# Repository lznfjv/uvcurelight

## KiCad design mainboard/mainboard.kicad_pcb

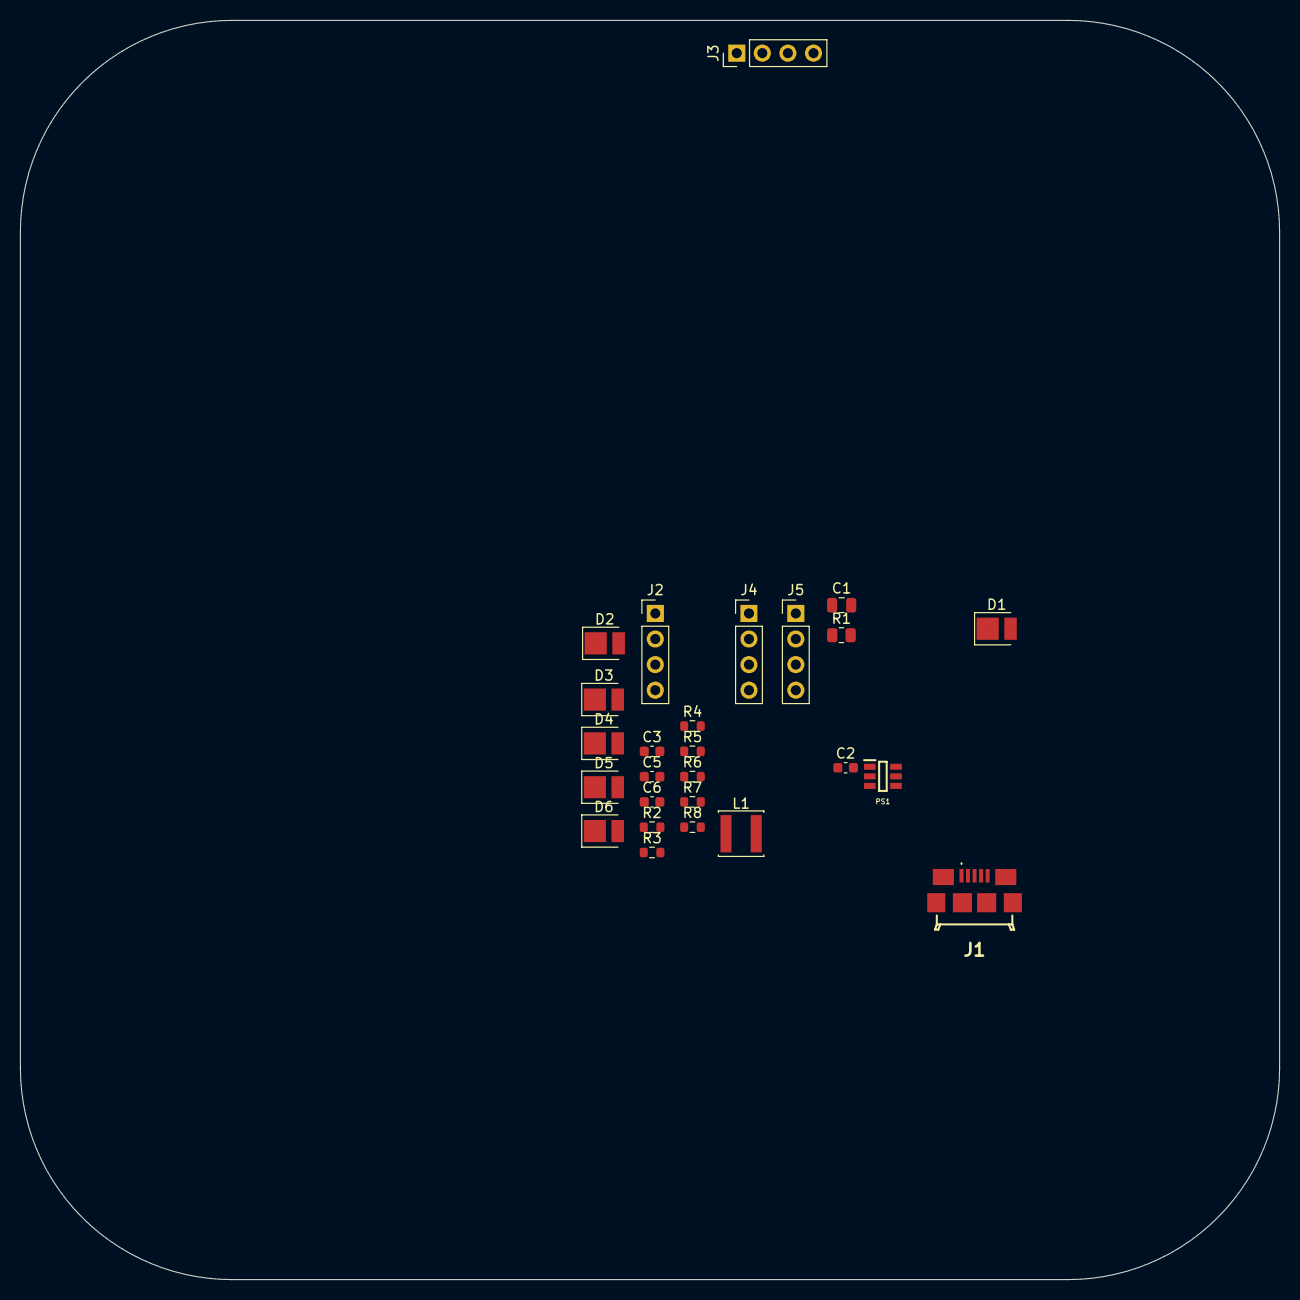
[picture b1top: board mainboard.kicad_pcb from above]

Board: 2 copper layers, 125.0 x 125.0 mm, 26 parts (0 on the bottom side), 12 nets, no tracks yet.

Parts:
C1: 10uF; C_0805_2012Metric
C2, C3: 22uF; C_0603_1608Metric
C5: 50pF; C_0603_1608Metric
C6: 330nF; C_0603_1608Metric
D1, D2, D3, D4, D5, D6: XL-2835UVA-02; LED_PLCC_2835
J1: 10118192-0001LF; 101181920001LF
J2, J3, J4, J5: 2.54-1*4P; PinHeader_1x04_P2.54mm_Vertical
L1: 3.3uH; L_Sunlord_SWPA4030S
PS1: AP62201WU-7; SOT95P280X100-6N
R1: 33.6k; R_0805_2012Metric
R2: 10k; R_0603_1608Metric
R3, R4, R5, R6, R7, R8: 3.3R; R_0603_1608Metric

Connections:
+5V: C1.1, J1.5, PS1.3 (VIN), PS1.5 (EN)
/+3.5V: C2.2, C3.2, C5.2, D1.2 (A), D2.2 (A), D3.2 (A), D4.2 (A), D5.2 (A), D6.2 (A), J2.1, J2.2, J3.1, J3.2, J4.1, J4.2, J5.1, J5.2, L1.2, R1.1
/BST: C6.2, PS1.6 (BST)
/FB: C5.1, PS1.4 (FB), R1.2, R2.1
/SW: C6.1, L1.1, PS1.2 (SW)
GND: C1.2, C2.1, C3.1, J1.1, J1.MP1, J2.3, J2.4, J3.3, J3.4, J4.3, J4.4, J5.3, J5.4, PS1.1 (GND), R2.2, R3.2, R4.2, R5.2, R6.2, R7.2, R8.2
unnamed: D1.1 (K), R3.1
unnamed: D2.1 (K), R4.1
unnamed: D3.1 (K), R5.1
unnamed: D4.1 (K), R6.1
unnamed: D5.1 (K), R7.1
unnamed: D6.1 (K), R8.1

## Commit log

2024-07-17 Layout mainboard, finish schematic
2024-07-17 Draw board outline
